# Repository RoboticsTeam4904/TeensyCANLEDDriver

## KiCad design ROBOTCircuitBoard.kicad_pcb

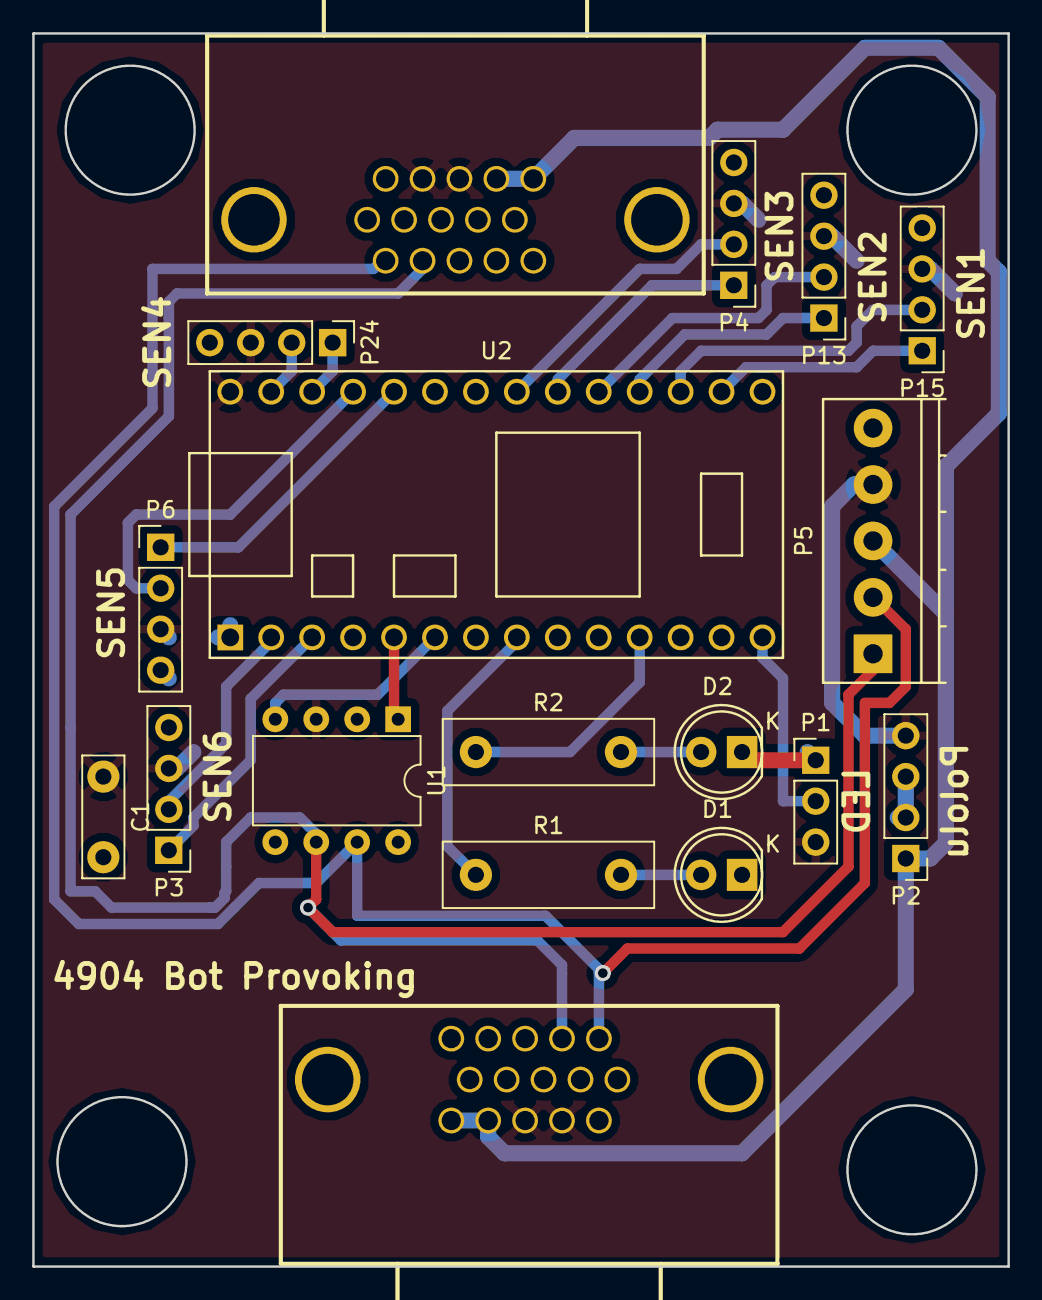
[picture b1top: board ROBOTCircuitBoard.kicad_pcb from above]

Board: 2 copper layers, 60.5 x 76.5 mm, 18 parts (0 on the bottom side), 24 nets.

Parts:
C1: C; C_Disc_D7.5mm_W2.5mm_P5.00mm
D1, D2: LED; LED-5MM
J1, J2: DB15_HighDensity_MountingHoles; conn_SPC15430
P1: CONN_01X03; Socket_Strip_Straight_1x03_Pitch2.54mm
P2, P3, P4, P6, P13, P15, P24: CONN_01X04; Socket_Strip_Straight_1x04_Pitch2.54mm
P5: CONN_01X05; TerminalBlock_Pheonix_PT-3.5mm_5pol
R1, R2: R; R_Box_L13.0mm_W4.0mm_P9.00mm
U1: MCP2551-I/P; DIP-8_W7.62mm
U2: Teensy3.2; Teensy30_31_32_LC_LessPins

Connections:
+5V: C1.1, J1.12, J1.13, J2.12, J2.13, P1.3, P2.4, P3.3, P4.3, P5.4, P6.3, P13.3, P15.3, P24.3, U1.3, U2.33
+12V: J1.14, J1.15, J2.14, J2.15, P2.1, P5.3
/0A: P3.2, U2.2
/0B: P3.1, U2.3
/1A: P4.1, U2.25
/1B: P4.2, U2.26
/A0: P15.1, U2.21
/A1: P15.2, U2.22
/A2: P13.1, U2.23
/A3: P13.2, U2.24
/A6: P6.1, U2.29
/A7: P6.2, U2.30
/A8: P24.1, U2.31
/A9: P24.2, U2.32
/CANH: J1.1, J2.1, P5.2, U1.7
/CANL: J1.2, J2.2, P5.1, U1.6
/CAN_Rx: U1.4, U2.6
/CAN_Tx: U1.1, U2.5
/DIN: P1.2, U2.14
GND: C1.2, D1.1, D2.1, J1.6, J1.7, J1.8, J1.9, J1.10, J2.6, J2.7, J2.8, J2.9, J2.10, P1.1, P2.2, P2.3, P3.4, P4.4, P5.5, P6.4, P13.4, P15.4, P24.4, U1.2, U1.8, U2.1
unnamed: D1.2, R1.2
unnamed: D2.2, R2.2
unnamed: R1.1, U2.8
unnamed: R2.1, U2.11

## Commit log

2017-02-20 Added four pin connectors, 5V layer, GND layer, and other misceallaneous jobs.
2017-02-21 added some 5v GND DATA DATA ports. Repositioned Pololu. Reduced board size slightly
2017-02-21 fixed board size
2017-03-11 added name and number
2017-03-22 changed footprints and updated part number
2017-03-22 Redid filled areas and labeled the 3-4 pin connecters and pololu port. Note: Silkscreen orientation will be looked into further.
2017-03-22 fixed silkscreen orientation
2017-03-23 Fixed silkscreen and began more organized board, not used.
2017-03-23 fixed silkscreen
